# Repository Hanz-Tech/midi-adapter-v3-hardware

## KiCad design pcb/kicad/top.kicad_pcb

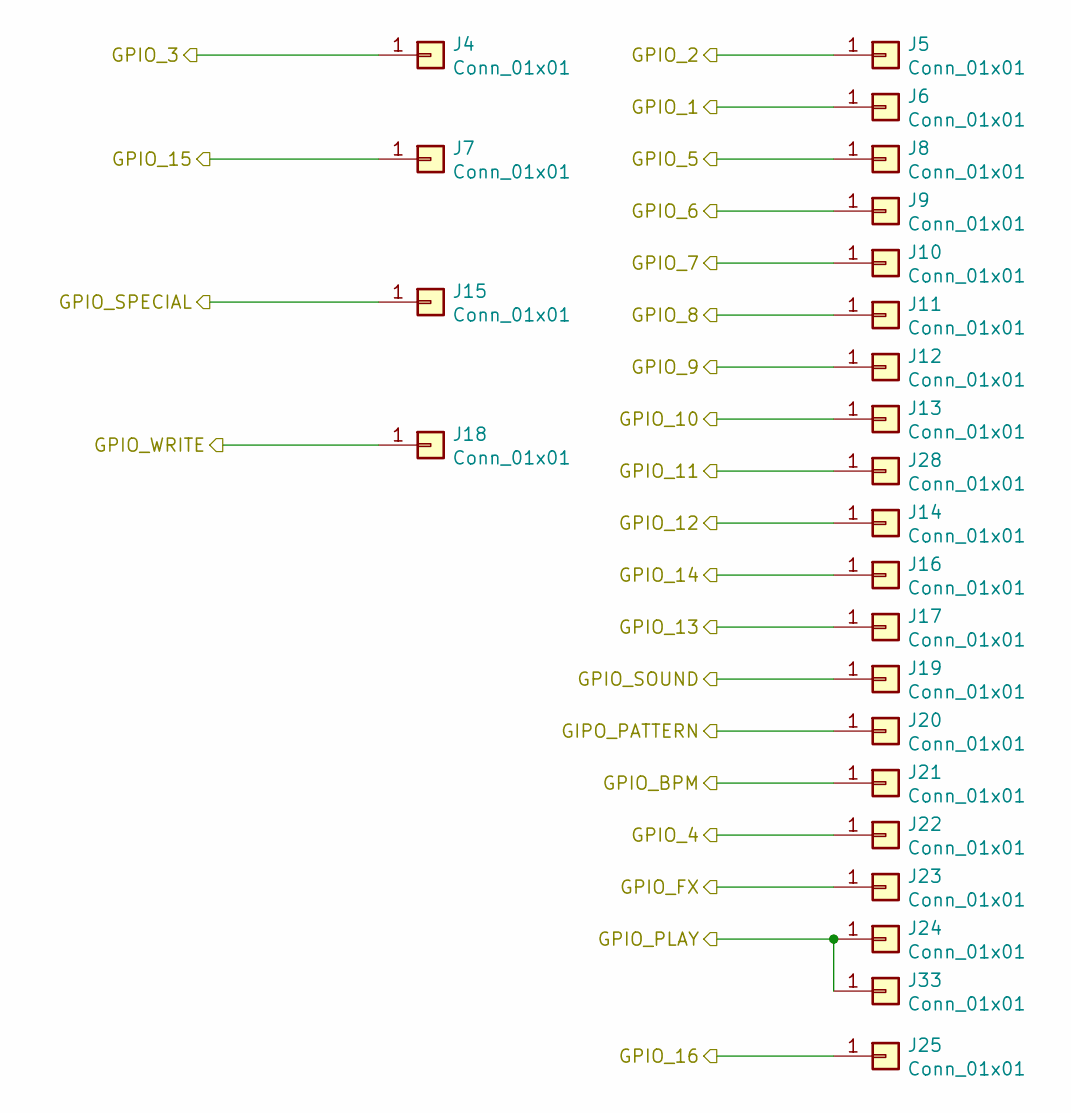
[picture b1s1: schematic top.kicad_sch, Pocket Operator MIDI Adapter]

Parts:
J4, J5, J6, J7, J8, J9, J10, J11, J12, J13, J14, J15, J16, J17, J18, J19, J20, J21, J22, J23, J24, J25, J28, J33: Conn_01x01; Pin_D1.0mm_L10.0mm

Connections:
Board_0-/top/GIPO_PATTERN: J20.1; also elsewhere on the board
Board_0-/top/GPIO_1: J6.1; also elsewhere on the board
Board_0-/top/GPIO_2: J5.1; also elsewhere on the board
Board_0-/top/GPIO_3: J4.1; also elsewhere on the board
Board_0-/top/GPIO_4: J22.1; also elsewhere on the board
Board_0-/top/GPIO_5: J8.1; also elsewhere on the board
Board_0-/top/GPIO_6: J9.1; also elsewhere on the board
Board_0-/top/GPIO_7: J10.1; also elsewhere on the board
Board_0-/top/GPIO_8: J11.1; also elsewhere on the board
Board_0-/top/GPIO_9: J12.1; also elsewhere on the board
Board_0-/top/GPIO_10: J13.1; also elsewhere on the board
Board_0-/top/GPIO_11: J28.1; also elsewhere on the board
Board_0-/top/GPIO_12: J14.1; also elsewhere on the board
Board_0-/top/GPIO_13: J17.1; also elsewhere on the board
Board_0-/top/GPIO_14: J16.1; also elsewhere on the board
Board_0-/top/GPIO_15: J7.1; also elsewhere on the board
Board_0-/top/GPIO_16: J25.1; also elsewhere on the board
Board_0-/top/GPIO_BPM: J21.1; also elsewhere on the board
Board_0-/top/GPIO_FX: J23.1; also elsewhere on the board
Board_0-/top/GPIO_PLAY: J24.1, J33.1; also elsewhere on the board
Board_0-/top/GPIO_SOUND: J19.1; also elsewhere on the board
Board_0-/top/GPIO_SPECIAL: J15.1; also elsewhere on the board
Board_0-/top/GPIO_WRITE: J18.1; also elsewhere on the board

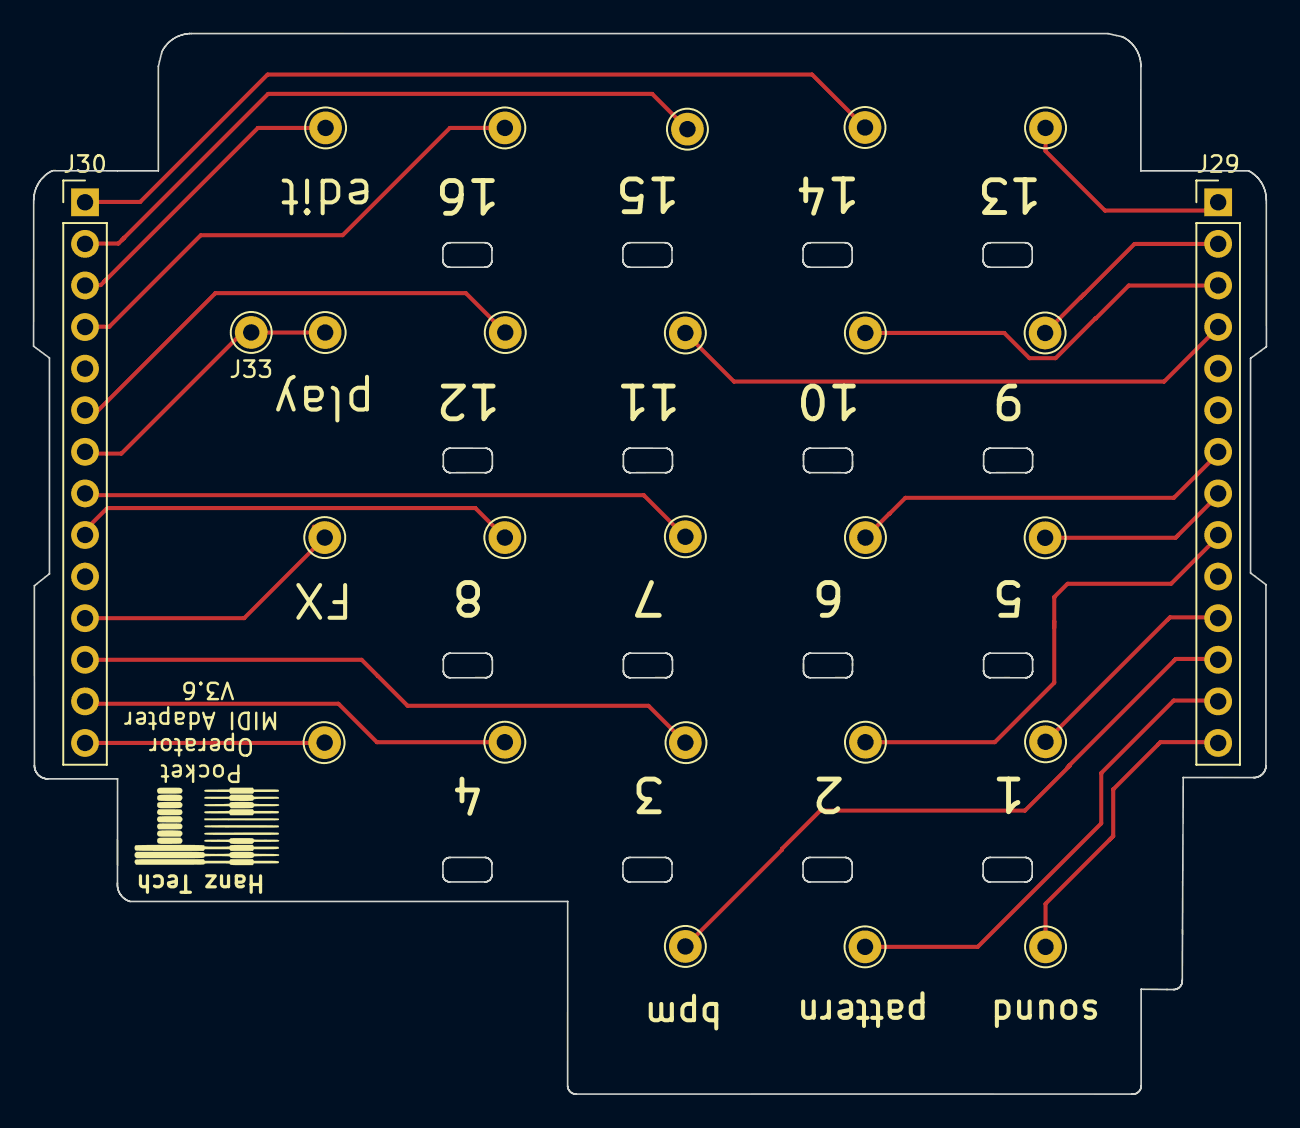
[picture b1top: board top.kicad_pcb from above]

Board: 2 copper layers, 75.3 x 64.8 mm, 26 parts (0 on the bottom side), 23 nets.

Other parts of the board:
J29, J30: Conn_01x14_Male; PinHeader_1x14_P2.54mm_Vertical

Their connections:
Board_0-/top/GIPO_PATTERN: J29.13; also elsewhere on the board
Board_0-/top/GPIO_1: J29.11; also elsewhere on the board
Board_0-/top/GPIO_2: J29.9; also elsewhere on the board
Board_0-/top/GPIO_3: J30.12; also elsewhere on the board
Board_0-/top/GPIO_4: J30.13; also elsewhere on the board
Board_0-/top/GPIO_5: J29.8; also elsewhere on the board
Board_0-/top/GPIO_6: J29.7; also elsewhere on the board
Board_0-/top/GPIO_7: J30.8; also elsewhere on the board
Board_0-/top/GPIO_8: J30.9; also elsewhere on the board
Board_0-/top/GPIO_9: J29.2; also elsewhere on the board
Board_0-/top/GPIO_10: J29.3; also elsewhere on the board
Board_0-/top/GPIO_11: J29.4; also elsewhere on the board
Board_0-/top/GPIO_12: J30.6; also elsewhere on the board
Board_0-/top/GPIO_13: J29.1; also elsewhere on the board
Board_0-/top/GPIO_14: J30.1; also elsewhere on the board
Board_0-/top/GPIO_15: J30.2; also elsewhere on the board
Board_0-/top/GPIO_16: J30.4; also elsewhere on the board
Board_0-/top/GPIO_BPM: J29.12; also elsewhere on the board
Board_0-/top/GPIO_FX: J30.11; also elsewhere on the board
Board_0-/top/GPIO_PLAY: J30.7; also elsewhere on the board
Board_0-/top/GPIO_SOUND: J29.14; also elsewhere on the board
Board_0-/top/GPIO_SPECIAL: J30.14; also elsewhere on the board
Board_0-/top/GPIO_WRITE: J30.3; also elsewhere on the board

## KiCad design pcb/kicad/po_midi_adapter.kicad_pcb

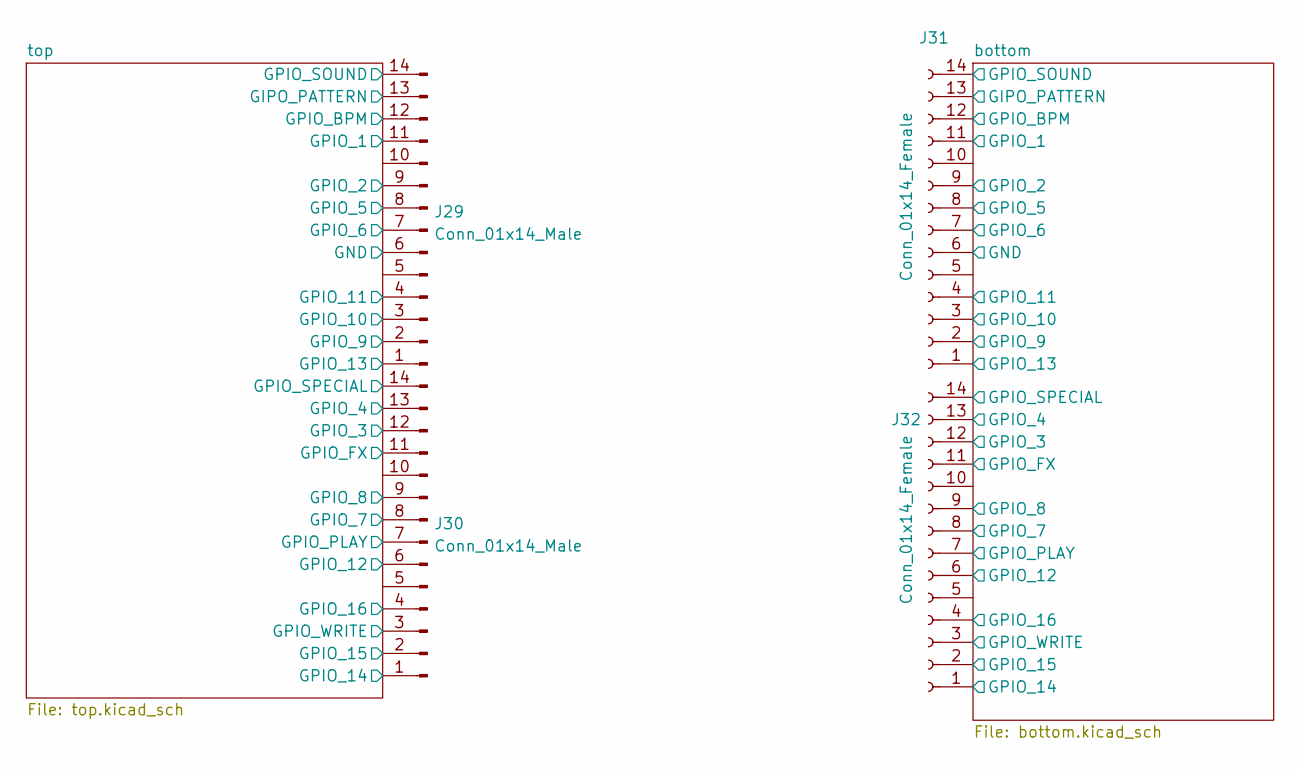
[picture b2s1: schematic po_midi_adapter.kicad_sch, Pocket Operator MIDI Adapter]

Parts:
J29, J30: Conn_01x14_Male; PinHeader_1x14_P2.54mm_Vertical
J31, J32: Conn_01x14_Female; PinHeader_1x14_P2.54mm_Vertical

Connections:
/GND: J29.6
/bottom/GIPO_PATTERN: J31.13; also elsewhere on the board
/bottom/GND: J31.6; also elsewhere on the board
/bottom/GPIO_1: J31.11; also elsewhere on the board
/bottom/GPIO_2: J31.9; also elsewhere on the board
/bottom/GPIO_3: J32.12; also elsewhere on the board
/bottom/GPIO_4: J32.13; also elsewhere on the board
/bottom/GPIO_5: J31.8; also elsewhere on the board
/bottom/GPIO_6: J31.7; also elsewhere on the board
/bottom/GPIO_7: J32.8; also elsewhere on the board
/bottom/GPIO_8: J32.9; also elsewhere on the board
/bottom/GPIO_9: J31.2; also elsewhere on the board
/bottom/GPIO_10: J31.3; also elsewhere on the board
/bottom/GPIO_11: J31.4; also elsewhere on the board
/bottom/GPIO_12: J32.6; also elsewhere on the board
/bottom/GPIO_13: J31.1; also elsewhere on the board
/bottom/GPIO_14: J32.1; also elsewhere on the board
/bottom/GPIO_15: J32.2; also elsewhere on the board
/bottom/GPIO_16: J32.4; also elsewhere on the board
/bottom/GPIO_BPM: J31.12; also elsewhere on the board
/bottom/GPIO_FX: J32.11; also elsewhere on the board
/bottom/GPIO_PLAY: J32.7; also elsewhere on the board
/bottom/GPIO_SOUND: J31.14; also elsewhere on the board
/bottom/GPIO_SPECIAL: J32.14; also elsewhere on the board
/bottom/GPIO_WRITE: J32.3; also elsewhere on the board
/top/GIPO_PATTERN: J29.13; also elsewhere on the board
/top/GPIO_1: J29.11; also elsewhere on the board
/top/GPIO_2: J29.9; also elsewhere on the board
/top/GPIO_3: J30.12; also elsewhere on the board
/top/GPIO_4: J30.13; also elsewhere on the board
/top/GPIO_5: J29.8; also elsewhere on the board
/top/GPIO_6: J29.7; also elsewhere on the board
/top/GPIO_7: J30.8; also elsewhere on the board
/top/GPIO_8: J30.9; also elsewhere on the board
/top/GPIO_9: J29.2; also elsewhere on the board
/top/GPIO_10: J29.3; also elsewhere on the board
/top/GPIO_11: J29.4; also elsewhere on the board
/top/GPIO_12: J30.6; also elsewhere on the board
/top/GPIO_13: J29.1; also elsewhere on the board
/top/GPIO_14: J30.1; also elsewhere on the board
/top/GPIO_15: J30.2; also elsewhere on the board
/top/GPIO_16: J30.4; also elsewhere on the board
/top/GPIO_BPM: J29.12; also elsewhere on the board
/top/GPIO_FX: J30.11; also elsewhere on the board
/top/GPIO_PLAY: J30.7; also elsewhere on the board
/top/GPIO_SOUND: J29.14; also elsewhere on the board
/top/GPIO_SPECIAL: J30.14; also elsewhere on the board
/top/GPIO_WRITE: J30.3; also elsewhere on the board

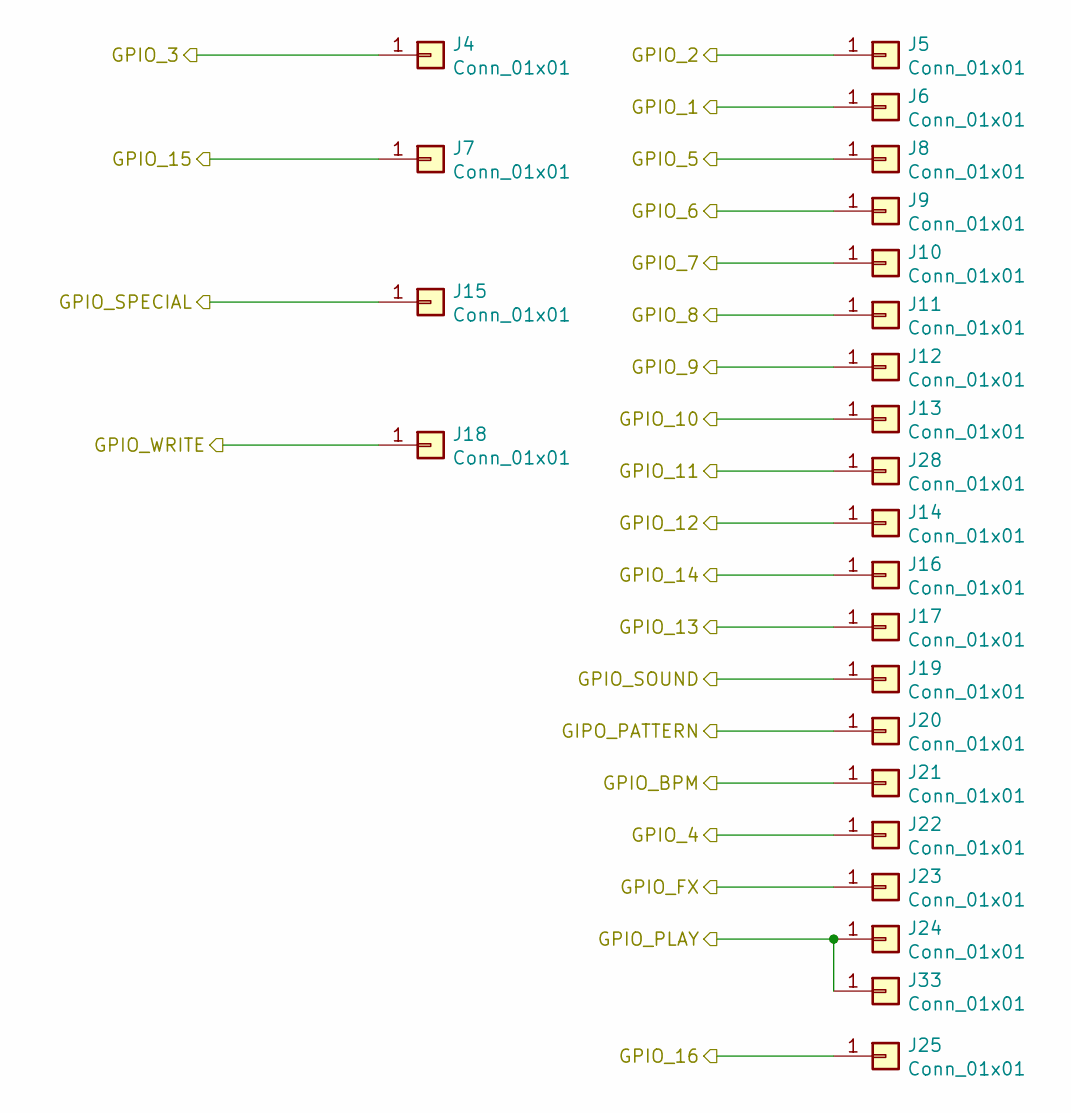
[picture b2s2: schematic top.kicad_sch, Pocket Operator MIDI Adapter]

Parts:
J4, J5, J6, J7, J8, J9, J10, J11, J12, J13, J14, J15, J16, J17, J18, J19, J20, J21, J22, J23, J24, J25, J28, J33: Conn_01x01; Pin_D1.0mm_L10.0mm

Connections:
/top/GIPO_PATTERN: J20.1; also elsewhere on the board
/top/GPIO_1: J6.1; also elsewhere on the board
/top/GPIO_2: J5.1; also elsewhere on the board
/top/GPIO_3: J4.1; also elsewhere on the board
/top/GPIO_4: J22.1; also elsewhere on the board
/top/GPIO_5: J8.1; also elsewhere on the board
/top/GPIO_6: J9.1; also elsewhere on the board
/top/GPIO_7: J10.1; also elsewhere on the board
/top/GPIO_8: J11.1; also elsewhere on the board
/top/GPIO_9: J12.1; also elsewhere on the board
/top/GPIO_10: J13.1; also elsewhere on the board
/top/GPIO_11: J28.1; also elsewhere on the board
/top/GPIO_12: J14.1; also elsewhere on the board
/top/GPIO_13: J17.1; also elsewhere on the board
/top/GPIO_14: J16.1; also elsewhere on the board
/top/GPIO_15: J7.1; also elsewhere on the board
/top/GPIO_16: J25.1; also elsewhere on the board
/top/GPIO_BPM: J21.1; also elsewhere on the board
/top/GPIO_FX: J23.1; also elsewhere on the board
/top/GPIO_PLAY: J24.1, J33.1; also elsewhere on the board
/top/GPIO_SOUND: J19.1; also elsewhere on the board
/top/GPIO_SPECIAL: J15.1; also elsewhere on the board
/top/GPIO_WRITE: J18.1; also elsewhere on the board

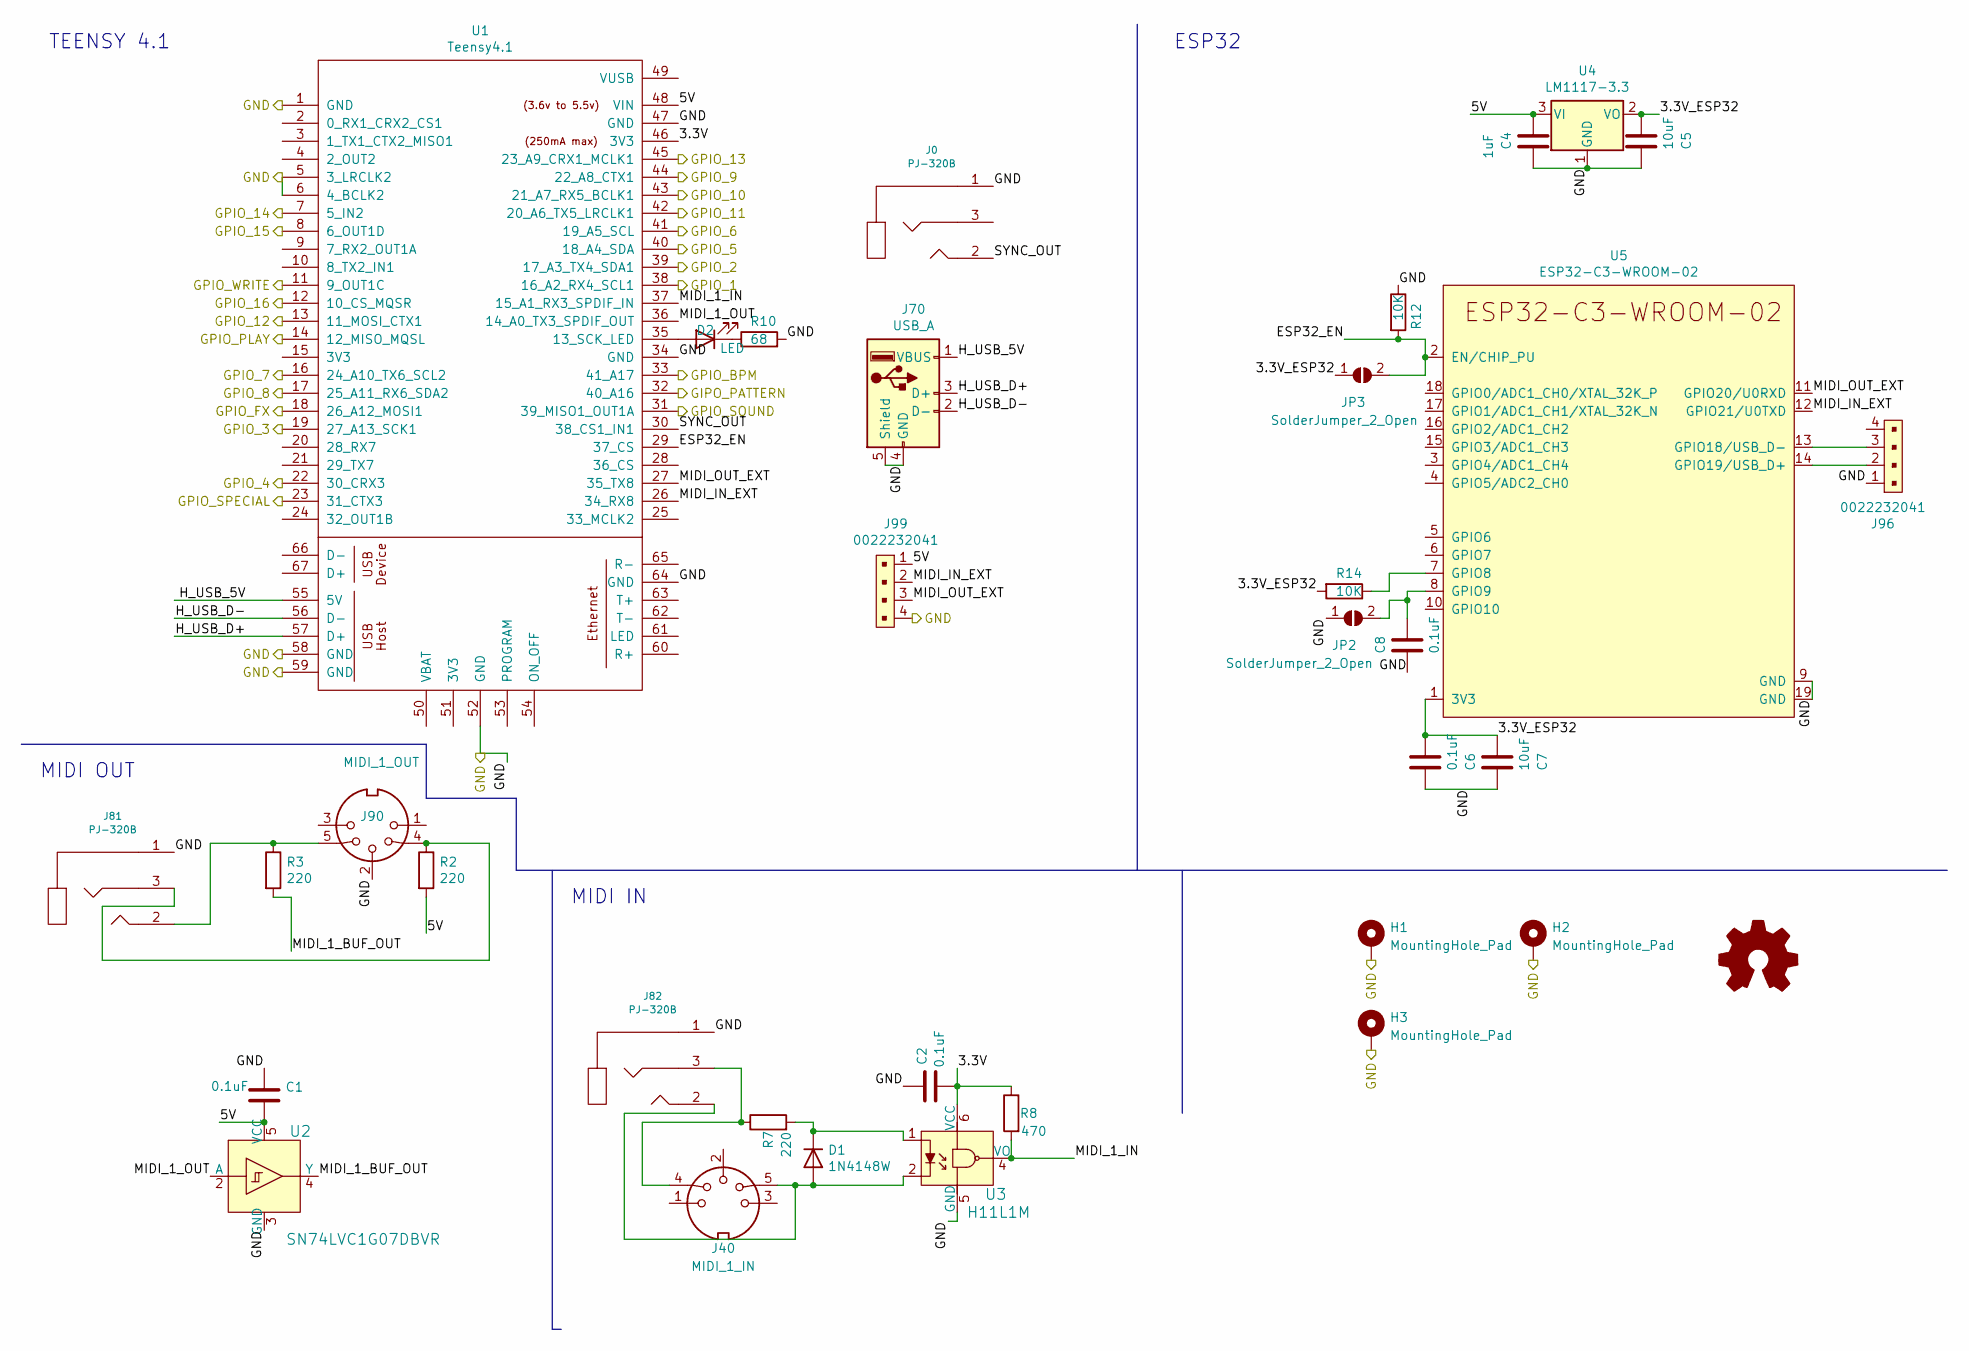
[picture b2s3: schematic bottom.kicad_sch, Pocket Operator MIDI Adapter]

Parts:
C1, C2, C6, C8: 0.1uF; C_0805_2012Metric_Pad1.18x1.45mm_HandSolder; LCSC C28233
C4: 1uF; C_0805_2012Metric_Pad1.18x1.45mm_HandSolder; LCSC C28323
C5, C7: 10uF; C_0805_2012Metric_Pad1.18x1.45mm_HandSolder; LCSC C440198
D1: 1N4148W; D_SOD-123; LCSC C81598
D2: LED; LED_0805_2012Metric_Pad1.15x1.40mm_HandSolder; LCSC C401117
H1, H2, H3: MountingHole_Pad; MountingHole_2.7mm_M2.5_ISO7380_Pad
J0: PJ-320B; 3.5mm_stereo_jack_PJ320B_THRU
J40: MIDI_1_IN; MIDI_DIN5_NO_ATTACHEMENT
J70: USB_A; TE_292303-1
J81, J82: PJ-320B; 3.5mm_stereo_jack_PJ320B
J90: MIDI_1_OUT; MIDI_DIN5_NO_ATTACHEMENT
J96: 0022232041; PinHeader_1x4_P2.54mm_Drill1.02mm; MPN 0022232041; Digi-Key_PN WM4202-ND
J99: 0022232041; PinHeader_1x4_P2.54mm_Drill1.02mm; Digi-Key_PN WM4202-ND
JP2, JP3: SolderJumper_2_Open; SolderJumper-2_P1.3mm_Open_Pad1.0x1.5mm
R2, R3, R7: 220; R_0805_2012Metric_Pad1.20x1.40mm_HandSolder; LCSC C17557
R8: 470; R_0805_2012Metric_Pad1.20x1.40mm_HandSolder; LCSC C17710
R10: 68; R_0805_2012Metric_Pad1.20x1.40mm_HandSolder; LCSC C17784
R12, R14: 10K; R_0805_2012Metric_Pad1.20x1.40mm_HandSolder; LCSC C17414
U1: Teensy4.1; Teensy41_poma
U2: SN74LVC1G07DBVR; SOT-753; Digi-Key_PN 296-8485-1-ND
U3: H11L1M; IC_H11L1SM; Digi-Key_PN H11L1-MQT-ND
U4: LM1117-3.3; SOT-89-3; MPN AZ1117CR-3.3TRG1; LCSC C5120796
U5: ESP32-C3-WROOM-02; LCSC C2934560

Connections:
/bottom/3.3V: C2.2, R8.1, U1.46 (3V3), U3.6 (VCC)
/bottom/3.3V_ESP32: C5.1, C6.1, C7.1, JP3.1 (A), R14.2, U4.2 (VO), U5.1 (3V3)
/bottom/5V: C1.2, C4.1, J99.1, R2.2, U1.48 (VIN), U2.5 (VCC), U4.3 (VI)
/bottom/ESP32_EN: JP3.2 (B), R12.2, U1.29 (37_CS), U5.2 (EN/CHIP_PU)
/bottom/GIPO_PATTERN: U1.32 (40_A16); also elsewhere on the board
/bottom/GND: C1.1, C2.1, C4.2, C5.2, C6.2, C7.2, C8.2, H1.1, H2.1, H3.1, J0.1, J70.4 (GND), J70.5 (Shield), J81.1, J82.1, J90.2, J96.1, J99.4, JP2.1 (A), R10.2, R12.1, U1.1 (GND), U1.5 (3_LRCLK2), U1.6 (4_BCLK2), U1.34 (GND), U1.47 (GND), U1.52 (GND), U1.58 (GND), U1.59 (GND), U1.64 (GND), U2.3 (GND), U3.5 (GND), U4.1 (GND), U5.9 (GND), U5.19 (GND); also elsewhere on the board
/bottom/GPIO_1: U1.38 (16_A2_RX4_SCL1); also elsewhere on the board
/bottom/GPIO_2: U1.39 (17_A3_TX4_SDA1); also elsewhere on the board
/bottom/GPIO_3: U1.19 (27_A13_SCK1); also elsewhere on the board
/bottom/GPIO_4: U1.22 (30_CRX3); also elsewhere on the board
/bottom/GPIO_5: U1.40 (18_A4_SDA); also elsewhere on the board
/bottom/GPIO_6: U1.41 (19_A5_SCL); also elsewhere on the board
/bottom/GPIO_7: U1.16 (24_A10_TX6_SCL2); also elsewhere on the board
/bottom/GPIO_8: U1.17 (25_A11_RX6_SDA2); also elsewhere on the board
/bottom/GPIO_9: U1.44 (22_A8_CTX1); also elsewhere on the board
/bottom/GPIO_10: U1.43 (21_A7_RX5_BCLK1); also elsewhere on the board
/bottom/GPIO_11: U1.42 (20_A6_TX5_LRCLK1); also elsewhere on the board
/bottom/GPIO_12: U1.13 (11_MOSI_CTX1); also elsewhere on the board
/bottom/GPIO_13: U1.45 (23_A9_CRX1_MCLK1); also elsewhere on the board
/bottom/GPIO_14: U1.7 (5_IN2); also elsewhere on the board
/bottom/GPIO_15: U1.8 (6_OUT1D); also elsewhere on the board
/bottom/GPIO_16: U1.12 (10_CS_MQSR); also elsewhere on the board
/bottom/GPIO_BPM: U1.33 (41_A17); also elsewhere on the board
/bottom/GPIO_FX: U1.18 (26_A12_MOSI1); also elsewhere on the board
/bottom/GPIO_PLAY: U1.14 (12_MISO_MQSL); also elsewhere on the board
/bottom/GPIO_SOUND: U1.31 (39_MISO1_OUT1A); also elsewhere on the board
/bottom/GPIO_SPECIAL: U1.23 (31_CTX3); also elsewhere on the board
/bottom/GPIO_WRITE: U1.11 (9_OUT1C); also elsewhere on the board
/bottom/H_USB_5V: J70.1 (VBUS), U1.55 (5V)
/bottom/H_USB_D+: J70.3 (D+), U1.57 (D+)
/bottom/H_USB_D-: J70.2 (D-), U1.56 (D-)
/bottom/MIDI_1_BUF_OUT: R3.2, U2.4 (Y)
/bottom/MIDI_1_IN: R8.2, U1.37 (15_A1_RX3_SPDIF_IN), U3.4 (VO)
/bottom/MIDI_1_OUT: U1.36 (14_A0_TX3_SPDIF_OUT), U2.2 (A)
/bottom/MIDI_IN_EXT: J99.2, U1.26 (34_RX8), U5.12 (GPIO21/U0TXD)
/bottom/MIDI_OUT_EXT: J99.3, U1.27 (35_TX8), U5.11 (GPIO20/U0RXD)
/bottom/SYNC_OUT: J0.2, U1.30 (38_CS1_IN1)
unnamed: C8.1, JP2.2 (B), U5.8 (GPIO9)
unnamed: D1.1 (K), R7.2, U3.1
unnamed: D1.2 (A), J40.5, J82.2, U3.2
unnamed: D2.1 (K), R10.1
unnamed: D2.2 (A), U1.35 (13_SCK_LED)
unnamed: J40.4, J82.3, R7.1
unnamed: J81.2, J90.5, R3.1
unnamed: J81.3, J90.4, R2.1
unnamed: J96.2, U5.14 (GPIO19/USB_D+)
unnamed: J96.3, U5.13 (GPIO18/USB_D-)
unnamed: R14.1, U5.7 (GPIO8)

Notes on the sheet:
MIDI OUT
ESP32
MIDI IN
TEENSY 4.1

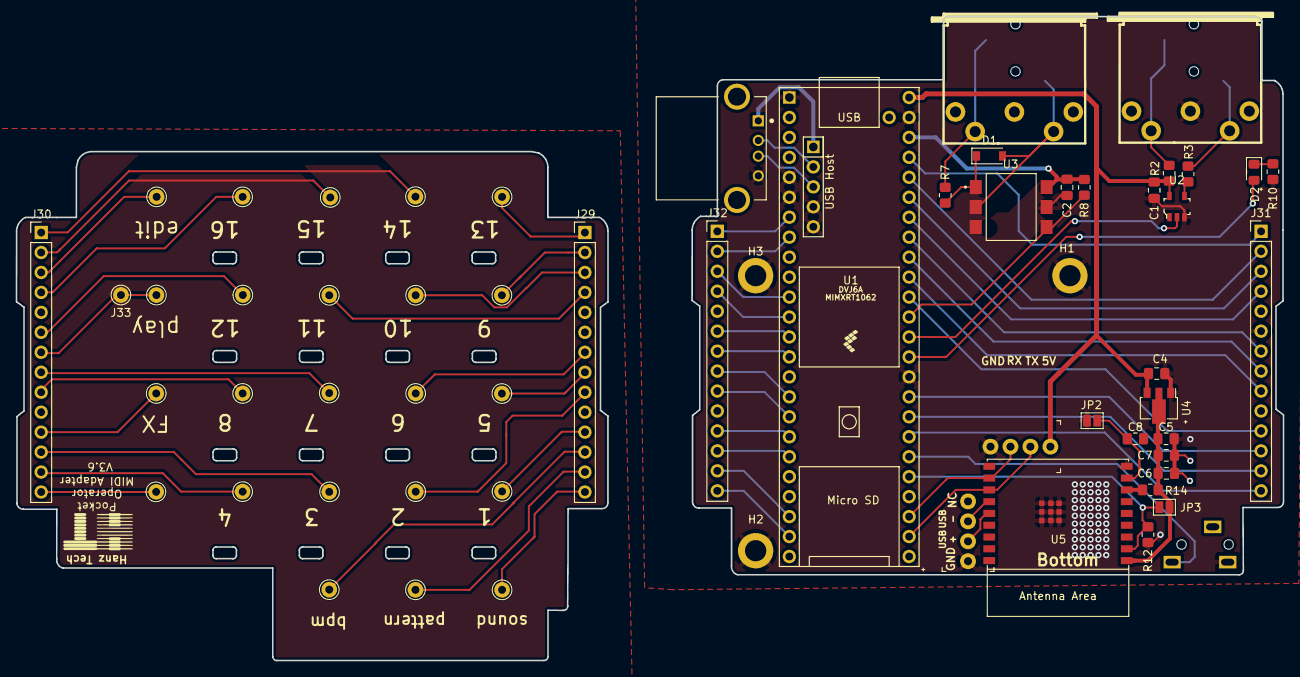
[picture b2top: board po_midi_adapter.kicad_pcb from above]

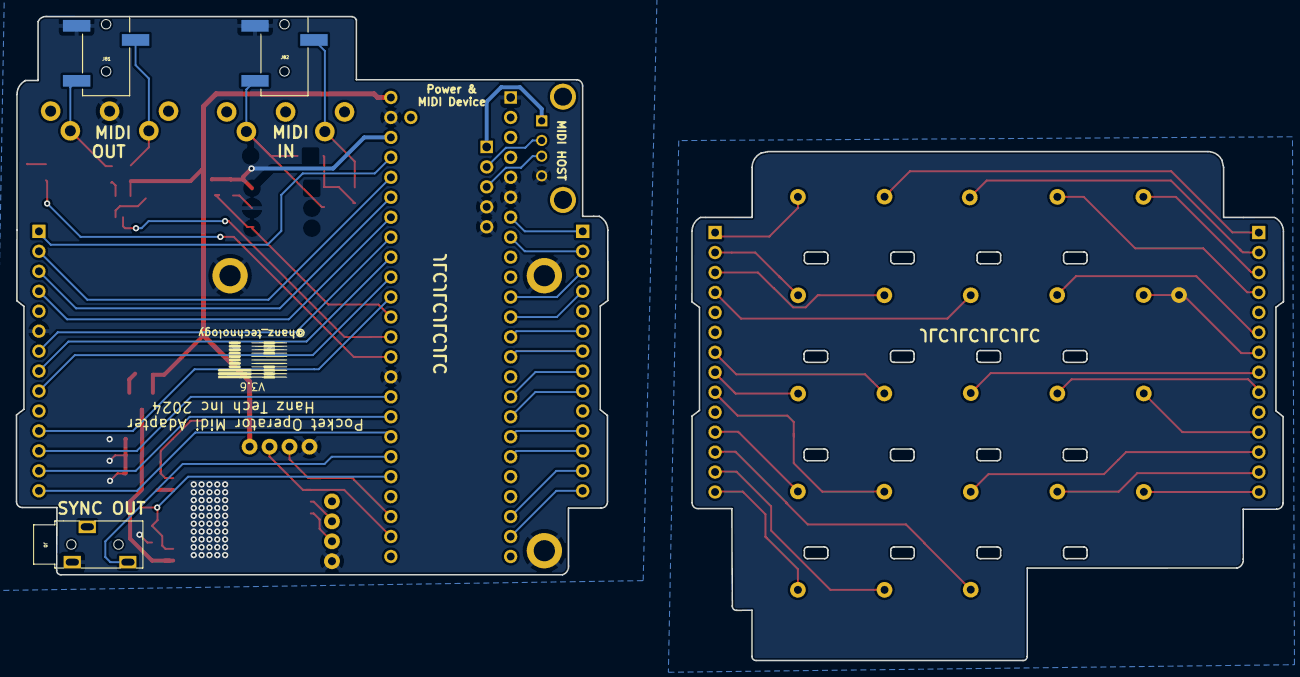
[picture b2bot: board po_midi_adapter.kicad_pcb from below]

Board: 2 copper layers, 161.2 x 82.0 mm, 62 parts (3 on the bottom side), 71 nets.

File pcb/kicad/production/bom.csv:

Designator,Footprint,Quantity,Value,LCSC Part #
C1,0805,1,0.1uF,C28233
C2,0805,1,0.1uF,C28233
C4,0805,1,1uF,C28323
C5,0805,1,10uF, C440198 
C6,0805,1,0.1uF,C28233
C7,0805,1,10uF, C440198 
C8,0805,1,0.1uF,C28233
D1,D_DO-35_SOD27_P7.62mm_Horizontal,1,1N914,
D2,0805,1,LED,C401117
"H1, H2, H3",MountingHole_2.7mm_M2.5_ISO7380_Pad,3,MountingHole_Pad,
J0,3.5mm_stereo_jack_PJ320B_THRU,1,PJ-320B,
"J31, J32",PinHeader_1x14_P2.54mm_Vertical,2,Conn_01x14_Female,
J40,MIDI_DIN5_NO_ATTACHEMENT,1,MIDI_1_IN,
J70,TE_292303-1,1,USB_A,
"J81, J82",3.5mm_stereo_jack_PJ320B,2,PJ-320B,
J90,MIDI_DIN5_NO_ATTACHEMENT,1,MIDI_1_OUT,
"J96, J99",PinHeader_1x4_P2.54mm_Drill1.02mm,2,0022232041,0022232041
"JP2, JP3",SolderJumper-2_P1.3mm_Open_Pad1.0x1.5mm,2,SolderJumper_2_Open,
R10,0805,1,68, C17784 
R12,0805,1,10K, C17414 
R14,0805,1,10K, C17414 
R2,0805,1,220, C17557 
R3,0805,1,220, C17557 
R7,0805,1,220, C17557 
R8,0805,1,470,C17710 
U1,Teensy41_poma,1,Teensy4.1,
U2,SOT-753,1,SN74LVC1G07DBVR,C7829
U3,DIP-6_W7.62mm,1,H11L1M,H11L1M
U4,SOT-89-3,1,LM1117-3.3, C5120796
U5,ESP32-C3-WROOM-02,1,ESP32-C3-WROOM-02,C2934560

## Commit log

2023-01-30 added backup cads
2023-01-30 removed old backup, replaced switch with jumper
2023-02-01 update to 3.5 bottom board
2023-02-07 updated bom
2023-02-09 update bottom pcb
2024-01-27 update cad
2024-12-08 update bom
